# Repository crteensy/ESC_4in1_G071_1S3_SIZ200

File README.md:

# ESC_4in1_G071_1S3_SIZ200

## UNTESTED
The G071+NCP81161 combo was successfully tested (with PSMN1R8-30MLHX though).

## Description
KiCad project for a 20mm 4in1 ESC
- 4 layers for prototyping
- no part smaller than 0402
- 1-3 S
- STM32G071
- NCP81161 gate drivers
- SIZ200
- 0m5 current sense shunt with INA186
- 5V reg: TPS630701; max 2A (VBat = 5 V)

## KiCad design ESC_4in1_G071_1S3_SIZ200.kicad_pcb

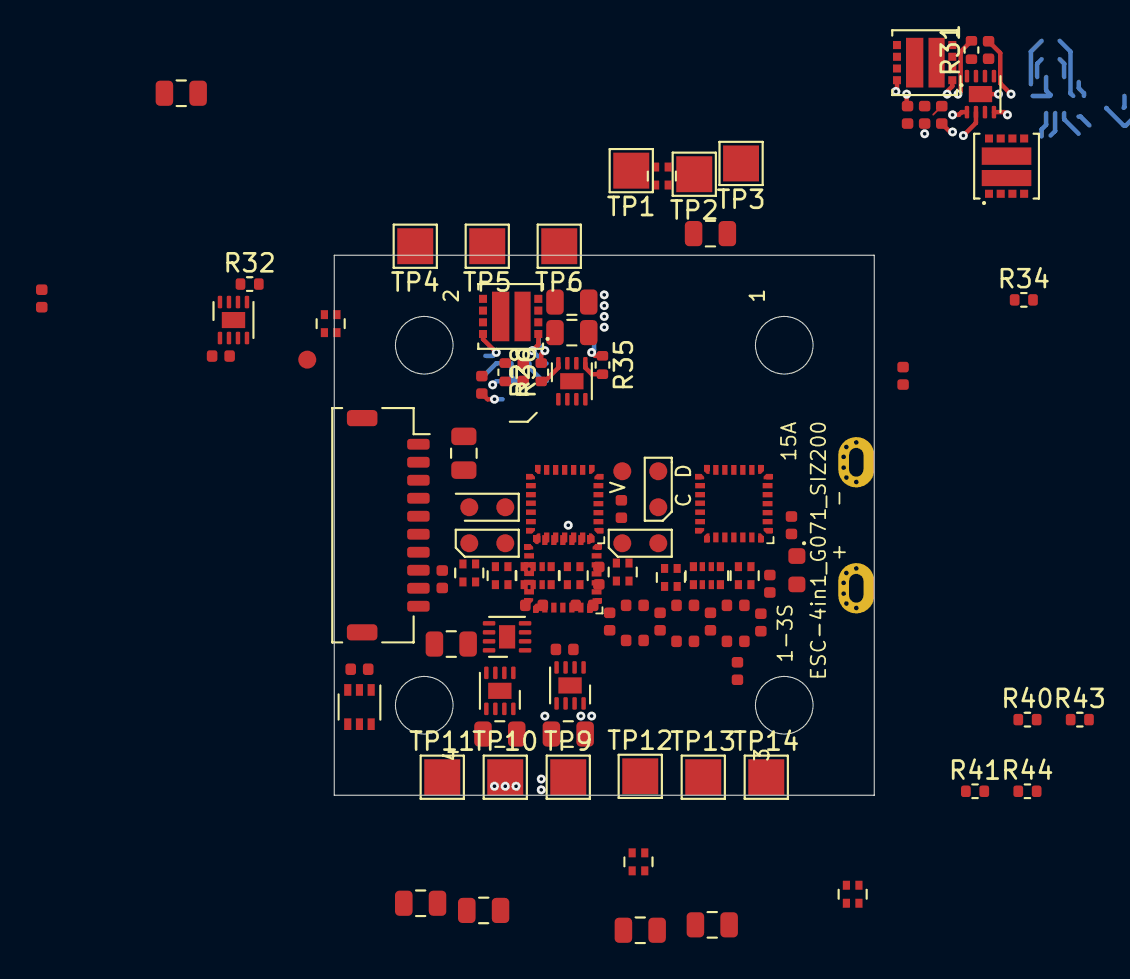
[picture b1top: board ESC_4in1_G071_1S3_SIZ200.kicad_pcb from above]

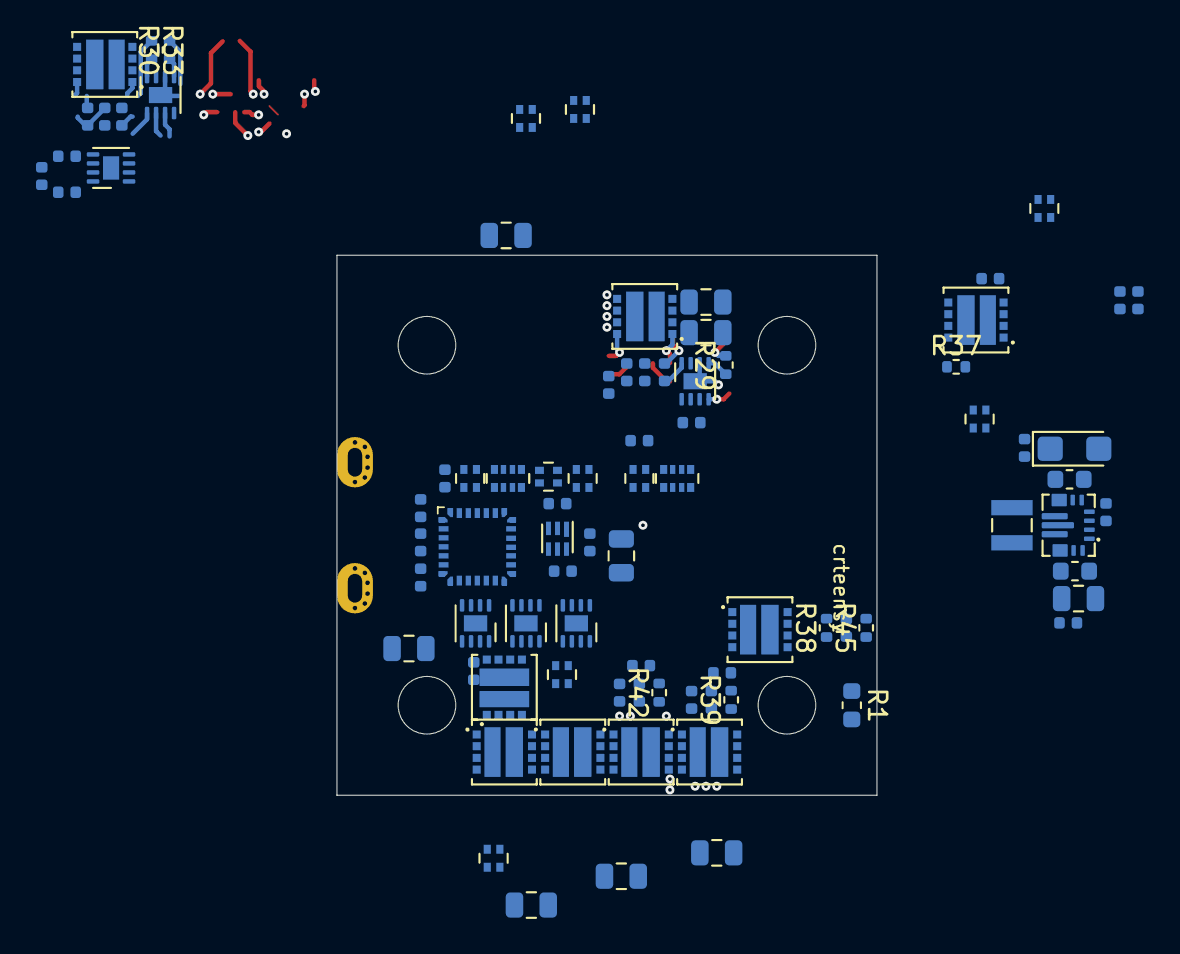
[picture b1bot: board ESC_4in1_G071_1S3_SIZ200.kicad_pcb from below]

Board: 6 copper layers, 30.0 x 30.0 mm, 191 parts (85 on the bottom side), 146 nets.

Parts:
C1, C2, C3, C8, C10, C12, C17, C21, C22, C24, C25, C27, C29, C31, C32, C34, C36, C63: 100n; C_0402_1005Metric
C4, C5, C6, C7, C9, C11, C23, C26, C28, C30, C33, C35: 1u; C_0402_1005Metric
C13: 10u; C_0805_2012Metric_dense
C14, C15: 10u; C_0603_1608Metric_dense
C16: 100u; CP_EIA-3216-10_Kemet-I
C18, C19: 2u2; C_0402_1005Metric
C20: 10n; C_0402_1005Metric
C37, C38, C39, C40, C41, C42, C43, C44, C45, C46, C47, C48, C49, C50, C51, C52, C53, C54, C55, C56: 22u; C_0805_2012Metric_dense
C70: 10u; C_0402_1005Metric
D1: LED; LED_0603_1608Metric
FB1, FB2: Ferrite_Bead_Small; L_0402_1005Metric
H1, H2, H3, H4: MountingHole; MountingHole_3.2mm_4mm
J1: Conn_01x10; JST_SHL_SM10B-SHLS-TF_1x10-1MP_P1.00mm_Horizontal_dense
L1: 820 nH; L_Wuerth_MAPI-2510
R1: 0m5; C_0603_1608Metric_dense
R2, R6, R10, R14, R18, R36, R37: 10k; R_0402_1005Metric
R3, R4, R5, R7, R8, R9, R11, R12, R13, R15, R16, R17: 4k7; R_0402_1005Metric
R19, R20, R21, R22, R23, R24, R25, R26, R28, R29, R30, R31, R32, R33, R34, R35, R38, R39, R40, R41, R42, R43, R44, R45: 10R0; R_0402_1005Metric
R27: 1k; R_0402_1005Metric
RN1, RN3, RN4, RN6, RN14, RN19, RN20, RN22: 10R0; R_Array_Convex_2x0402_dense
RN2, RN5, RN13, RN16: 1k; R_Array_Convex_2x0402_dense
RN7, RN11, RN17, RN23: 2k2; R_Array_Convex_2x0402_dense
RN8, RN10, RN15, RN21: 10k; R_Array_Convex_2x0402_dense
RN9, RN12, RN18, RN24: 2k2; R_Array_Convex_4x0402_dense
TP1, TP2, TP3, TP4, TP5, TP6, TP9, TP10, TP11, TP12, TP13, TP14: TestPoint_Flag; ESC_Pad_2.0x2.0mm
TP7, TP8: TestPoint_Flag; batt_pad_wide_relaxed
TP15, TP16, TP17, TP18, TP19, TP20, TP21, TP22, TP23, TP24: TestPoint; TestPoint_Pad_D1.0mm_dense
U1, U17, U21, U28: STM32G071GBU6; UFQFPN28
U2, U4, U6, U8, U10, U12, U18, U20, U23, U25, U27, U30: NCP81161MNTBG; DFN-8-1EP_2x2mm_P0.5mm_EP0.9x1.3mm_narrow
U3, U5, U7, U9, U11, U13, U19, U22, U24, U26, U29, U31: SIZ200DT-T1-GE3; PowerPAIR3.3x3.3_splitpaste
U14: TPS630701; TEXAS_15-VQFN-HR
U15: TPS72733DSE; WSON-6_1.5x1.5mm_P0.5mm
U16: INA186A2; SOT-363_SC-70-6

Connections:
+3V3: C19.2, C21.2, C22.2, C25.2, C32.2, C63.2, C70.2, D1.2, TP23.1, U1.3, U15.1, U17.3, U21.3, U28.3
+5V: C4.2, C5.2, C6.2, C7.2, C9.2, C11.2, C18.2, C23.2, C26.2, C28.2, C30.2, C33.2, C35.2, FB2.1, J1.9, R3.1, R4.1, R5.1, R7.1, R8.1, R9.1, R11.1, R12.1, R13.1, R15.1, R16.1, R17.1, U2.4, U4.4, U6.4, U8.4, U10.4, U12.4, U15.4, U15.6, U16.3, U18.4, U20.4, U23.4, U25.4, U27.4, U30.4
+BATT: C40.2, C41.2, C42.2, C43.2, C44.2, C45.2, C46.2, C47.2, C48.2, C49.2, C50.2, C51.2, C52.2, C53.2, C54.2, C55.2, C56.2, FB1.2, J1.2, R1.1, TP7.1, U3.2, U5.2, U7.2, U9.2, U11.2, U13.2, U16.4, U26.2, U29.2, U31.2
/ESC1_A: C1.1, RN8.2, TP1.1, U2.7, U3.3
/ESC1_A_DRVH: R33.2, U2.8
/ESC1_A_DRVL: R30.1, U2.5
/ESC1_A_EN: U1.22, U2.3
/ESC1_A_GH: R33.1, U3.1
/ESC1_A_GL: R30.2, U3.5
/ESC1_A_PWM: R3.2, U1.19, U2.2
/ESC1_B: C2.1, RN8.1, TP2.1, U4.7, U5.3
/ESC1_B_DRVH: R31.1, U4.8
/ESC1_B_DRVL: R26.2, U4.5
/ESC1_B_EN: U1.17, U4.3
/ESC1_B_GH: R31.2, U5.1
/ESC1_B_GL: R26.1, U5.5
/ESC1_B_PWM: R4.2, U1.18, U4.2
/ESC1_C: C3.1, R6.1, TP3.1, U6.7, U7.3
/ESC1_C_DRVH: R34.2, U6.8
/ESC1_C_DRVL: R22.2, U6.5
/ESC1_C_EN: U1.13, U6.3
/ESC1_C_GH: R34.1, U7.1
/ESC1_C_GL: R22.1, U7.5
/ESC1_C_PWM: R5.2, U1.16, U6.2
/ESC1_IN: RN13.4, U1.24
/ESC1_MA: RN8.3, RN9.1, RN9.2, U1.27
/ESC1_MB: RN8.4, RN9.3, RN9.4, U1.23
/ESC1_MC: R6.2, RN7.3, RN7.4, U1.8
/ESC1_SWDCLK: TP22.1, U1.21
/ESC1_SWDIO: TP20.1, U1.20
/ESC1_Y: RN7.1, RN9.6, RN9.8, U1.9
/ESC1_tele_o: RN2.4, U1.26
/ESC2_A: C8.1, R37.2, TP4.1, U8.7, U9.3
/ESC2_A_DRVH: R19.2, U8.8
/ESC2_A_DRVL: R32.2, U8.5
/ESC2_A_EN: U8.3, U17.22
/ESC2_A_GH: R19.1, U9.1
/ESC2_A_GL: R32.1, U9.5
/ESC2_A_PWM: R7.2, U8.2, U17.19
/ESC2_B: C10.1, R36.1, TP5.1, U10.7, U11.3
/ESC2_B_DRVH: R23.2, U10.8
/ESC2_B_DRVL: R29.1, U10.5
/ESC2_B_EN: U10.3, U17.17
/ESC2_B_GH: R23.1, U11.1
/ESC2_B_GL: R29.2, U11.5
/ESC2_B_PWM: R8.2, U10.2, U17.18
/ESC2_C: C12.1, R10.1, TP6.1, U12.7, U13.3
/ESC2_C_DRVH: R28.1, U12.8
/ESC2_C_DRVL: R35.2, U12.5
/ESC2_C_EN: U12.3, U17.13
/ESC2_C_GH: R28.2, U13.1
/ESC2_C_GL: R35.1, U13.5
/ESC2_C_PWM: R9.2, U12.2, U17.16
/ESC2_IN: RN13.3, U17.24
/ESC2_MA: R37.1, RN12.1, RN12.2, U17.27
/ESC2_MB: R36.2, RN12.3, RN12.4, U17.23
/ESC2_MC: R10.2, RN11.3, RN11.4, U17.8
/ESC2_SWDCLK: TP18.1, U17.21
/ESC2_SWDIO: TP16.1, U17.20
/ESC2_Y: RN11.1, RN12.6, RN12.8, U17.9
/ESC2_tele_o: RN2.3, U17.26
/ESC3_A: C31.1, RN21.1, TP12.1, U25.7, U26.3
/ESC3_A_DRVH: R43.2, U25.8
/ESC3_A_DRVL: R44.2, U25.5
/ESC3_A_EN: U25.3, U28.22
/ESC3_A_GH: R43.1, U26.1
/ESC3_A_GL: R44.1, U26.5
/ESC3_A_PWM: R15.2, U25.2, U28.19
/ESC3_B: C34.1, RN21.2, TP13.1, U27.7, U29.3
/ESC3_B_DRVH: R41.2, U27.8
/ESC3_B_DRVL: R25.2, U27.5
/ESC3_B_EN: U27.3, U28.17
/ESC3_B_GH: R41.1, U29.1
/ESC3_B_GL: R25.1, U29.5
/ESC3_B_PWM: R16.2, U27.2, U28.18
/ESC3_C: C36.1, R18.1, TP14.1, U30.7, U31.3
/ESC3_C_DRVH: R40.2, U30.8
/ESC3_C_DRVL: R21.2, U30.5
/ESC3_C_EN: U28.13, U30.3
/ESC3_C_GH: R40.1, U31.1
/ESC3_C_GL: R21.1, U31.5
/ESC3_C_PWM: R17.2, U28.16, U30.2
/ESC3_IN: RN16.4, U28.24
/ESC3_MA: RN21.4, RN24.1, RN24.2, U28.27
/ESC3_MB: RN21.3, RN24.3, RN24.4, U28.23
/ESC3_MC: R18.2, RN23.3, RN23.4, U28.8
/ESC3_SWDCLK: TP21.1, U28.21
/ESC3_SWDIO: TP19.1, U28.20
/ESC3_Y: RN23.1, RN24.6, RN24.8, U28.9
/ESC3_tele_o: RN5.4, U28.26
/ESC4_A: C24.1, RN15.1, TP9.1, U18.7, U19.3
/ESC4_A_DRVH: R24.2, U18.8
/ESC4_A_DRVL: R42.2, U18.5
/ESC4_A_EN: U18.3, U21.22
/ESC4_A_GH: R24.1, U19.1
/ESC4_A_GL: R42.1, U19.5
/ESC4_A_PWM: R11.2, U18.2, U21.19
/ESC4_B: C27.1, RN15.2, TP10.1, U20.7, U22.3
/ESC4_B_DRVH: R20.2, U20.8
/ESC4_B_DRVL: R39.2, U20.5
/ESC4_B_EN: U20.3, U21.17
/ESC4_B_GH: R20.1, U22.1
/ESC4_B_GL: R39.1, U22.5
/ESC4_B_PWM: R12.2, U20.2, U21.18
/ESC4_C: C29.1, R14.1, TP11.1, U23.7, U24.3
/ESC4_C_DRVH: R38.2, U23.8
/ESC4_C_DRVL: R45.2, U23.5
/ESC4_C_EN: U21.13, U23.3
/ESC4_C_GH: R38.1, U24.1
/ESC4_C_GL: R45.1, U24.5
/ESC4_C_PWM: R13.2, U21.16, U23.2
/ESC4_IN: RN16.3, U21.24
/ESC4_MA: RN15.4, RN18.1, RN18.2, U21.27
/ESC4_MB: RN15.3, RN18.3, RN18.4, U21.23
/ESC4_MC: R14.2, RN17.3, RN17.4, U21.8
/ESC4_SWDCLK: TP17.1, U21.21
/ESC4_SWDIO: TP15.1, U21.20
/ESC4_Y: RN17.1, RN18.6, RN18.8, U21.9
/ESC4_tele_o: RN5.3, U21.26
/ESCx_tele: J1.4, RN2.1, RN2.2, RN5.1, RN5.2
/IBat: C20.2, J1.3, R2.1
GND: C4.1, C5.1, C6.1, C7.1, C9.1, C11.1, C13.1, C14.1, C15.1, C16.2, C17.1, C18.1, C19.1, C20.1, C21.1, C22.1, C23.1, C25.1, C26.1, C28.1, C30.1, C32.1, C33.1, C35.1, C37.1, C38.1, C39.1, C40.1, C41.1, C42.1, C43.1, C44.1, C45.1, C46.1, C47.1, C48.1, C49.1, C50.1, C51.1, C52.1, C53.1, C54.1, C55.1, C56.1, C63.1, C70.1, J1.1, J1.10, R27.1, RN7.2, RN9.5, RN9.7, RN11.2, RN12.5, RN12.7, RN17.2, RN18.5, RN18.7, RN23.2, RN24.5, RN24.7, TP8.1, TP24.1, U1.4, U2.6, U2.9, U3.4, U4.6, U4.9, U5.4, U6.6, U6.9, U7.4, U8.6, U8.9, U9.4, U10.6, U10.9, U11.4, U12.6, U12.9, U13.4, U14.4, U14.6, U14.10, U14.15, U15.2, U15.3, U15.5, U16.1, U16.2, U17.4, U18.6, U18.9, U19.4, U20.6, U20.9, U21.4, U22.4, U23.6, U23.9, U24.4, U25.6, U25.9, U26.4, U27.6, U27.9, U28.4, U29.4, U30.6, U30.9, U31.4
unnamed: C1.2, U2.1
unnamed: C2.2, U4.1
unnamed: C3.2, U6.1
unnamed: C8.2, U8.1
unnamed: C10.2, U10.1
unnamed: C12.2, U12.1
unnamed: C13.2, C14.2, FB1.1, U14.1, U14.13, U14.14
unnamed: C15.2, C16.1, FB2.2, U14.5, U14.7
unnamed: C17.2, U14.3
unnamed: C24.2, U18.1
unnamed: C27.2, U20.1
unnamed: C29.2, U23.1
unnamed: C31.2, U25.1
unnamed: C34.2, U27.1
unnamed: C36.2, U30.1
unnamed: D1.1, R27.2
unnamed: J1.5, RN13.1
unnamed: J1.6, RN13.2
unnamed: J1.7, RN16.1
unnamed: J1.8, RN16.2
unnamed: L1.1, U14.9
unnamed: L1.2, U14.11
unnamed: R2.2, U16.6
VESC4: C37.2, C38.2, C39.2, R1.2, U16.5, U19.2, U22.2, U24.2

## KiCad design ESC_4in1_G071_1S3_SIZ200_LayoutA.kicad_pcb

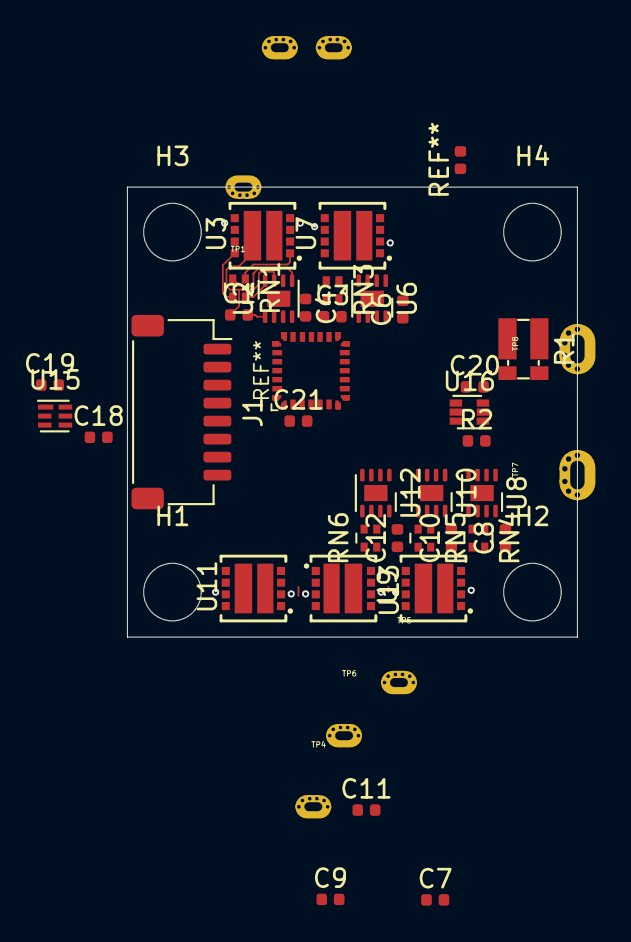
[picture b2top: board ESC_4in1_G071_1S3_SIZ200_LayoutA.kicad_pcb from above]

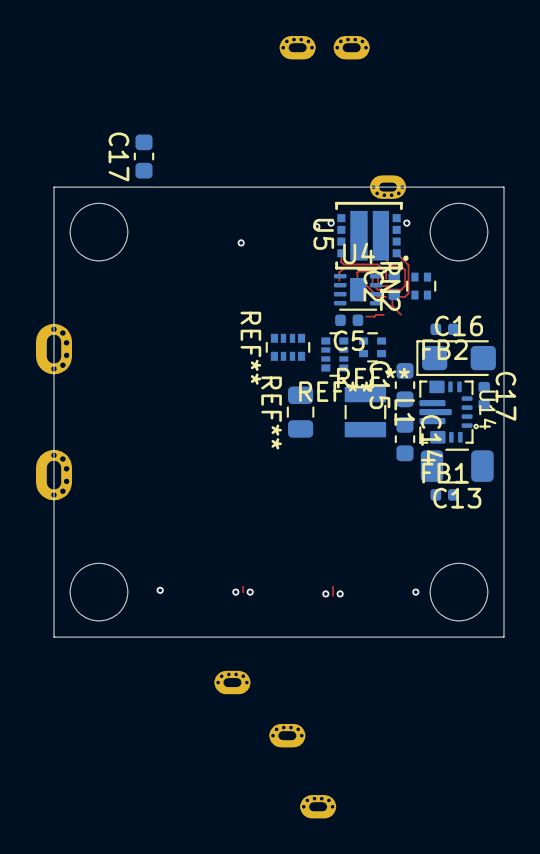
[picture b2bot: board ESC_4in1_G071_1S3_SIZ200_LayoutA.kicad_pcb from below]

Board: 2 copper layers, 25.0 x 25.0 mm, 62 parts (15 on the bottom side), 56 nets.

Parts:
C1, C2, C3, C4, C5, C6, C7, C8, C9, C10, C11, C12, C17, C21: 100n; C_0402_1005Metric
C13: 10u; C_1206_3216Metric_dense
C14, C15, C17#2: 10u; C_0603_1608Metric_dense
C16: 100u; CP_EIA-3216-10_Kemet-I
C18, C19: 2u2; C_0402_1005Metric
C20: 10n; C_0402_1005Metric
FB1, FB2: Ferrite_Bead_Small; L_0402_1005Metric
H1, H2, H3, H4: MountingHole; MountingHole_3.2mm_4mm
J1: Conn_01x08; JST_SH_SM08B-SRSS-TB_1x08-1MP_P1.00mm_Horizontal
L1: 1u; L_Wuerth_MAPI-2510
R1: R_Shunt; R_Shunt_Vishay_WSKW0612
R2: 10k; C_0402_1005Metric
RN1, RN2, RN3, RN4, RN5, RN6: 10R0; R_Array_Convex_2x0402
TP1, TP2, TP3, TP4, TP5, TP6: TestPoint_Flag; esc_pad
TP7, TP8: TestPoint_Flag; batt_pad_wide
U1: STM32G071GBU6; UFQFPN28
U2, U4, U6, U8, U10, U12: NCP81253MNTBG; DFN-8-1EP_2x2mm_P0.5mm_EP0.9x1.3mm_narrow
U3, U5, U7, U9, U11, U13: SIZ200DT-T1-GE3; PowerPAIR3.3x3.3
U14: TPS630701; TEXAS_15-VQFN-HR
U15: TPS727xxDSE; WSON-6_1.5x1.5mm_P0.5mm
U16: INA185; SOT-563

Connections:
+3V3: C19.2, C21.2, U15.1, U16.3
+5V: C4.2, C5.2, C6.2, C7.2, C9.2, C11.2, C18.2, FB2.1, U2.4, U4.4, U6.4, U8.4, U10.4, U12.4, U15.4, U15.6
+BATT: FB1.2, TP7.1, U3.2, U5.2, U7.2, U9.2, U11.2, U13.2
/ESC1_A: C1.1, TP1.1, U2.7, U3.3
/ESC1_A_EN: U1.15, U2.3
/ESC1_A_PWM: U1.19, U2.2
/ESC1_B: C2.1, TP2.1, U4.7, U5.3
/ESC1_B_EN: U1.14, U4.3
/ESC1_B_PWM: U1.18, U4.2
/ESC1_C: C3.1, TP3.1, U6.7, U7.3
/ESC1_C_EN: U1.13, U6.3
/ESC1_C_PWM: U1.16, U6.2
/ESC2_A: C8.1, TP4.1, U8.7, U9.3
/ESC2_B: C10.1, TP5.1, U10.7, U11.3
/ESC2_C: C12.1, TP6.1, U12.7, U13.3
/IBat: C20.2, R2.1
GND: C4.1, C5.1, C6.1, C7.1, C9.1, C11.1, C13.1, C14.1, C15.1, C16.2, C17.1, C18.1, C19.1, C20.1, C21.1, R1.4, U2.6, U2.9, U3.4, U4.6, U4.9, U5.4, U6.6, U6.9, U7.4, U8.6, U8.9, U9.4, U10.6, U10.9, U11.4, U12.6, U12.9, U13.4, U14.4, U14.6, U14.10, U14.15, U15.2, U15.3, U15.5, U16.1, U16.2
unnamed: C1.2, U2.1
unnamed: C2.2, U4.1
unnamed: C3.2, U6.1
unnamed: C8.2, U8.1
unnamed: C10.2, U10.1
unnamed: C12.2, U12.1
unnamed: C13.2, C14.2, FB1.1, U14.1, U14.13, U14.14
unnamed: C15.2, C16.1, FB2.2, U14.5, U14.7
unnamed: C17.2, U14.3
unnamed: L1.1, U14.9
unnamed: L1.2, U14.11
unnamed: R1.1, TP8.1
unnamed: R1.2, U16.4
unnamed: R1.3, U16.5
unnamed: R2.2, U16.6
unnamed: RN1.1, U3.1
unnamed: RN1.2, U2.5
unnamed: RN1.3, U3.5
unnamed: RN1.4, U2.8
unnamed: RN2.1, U4.8
unnamed: RN2.2, U4.5
unnamed: RN2.3, U5.5
unnamed: RN2.4, U5.1
unnamed: RN3.1, U7.1
unnamed: RN3.2, U6.5
unnamed: RN3.3, U7.5
unnamed: RN3.4, U6.8
unnamed: RN4.1, U9.1
unnamed: RN4.2, U8.5
unnamed: RN4.3, U9.5
unnamed: RN4.4, U8.8
unnamed: RN5.1, U10.8
unnamed: RN5.2, U10.5
unnamed: RN5.3, U11.5
unnamed: RN5.4, U11.1
unnamed: RN6.1, U13.5
unnamed: RN6.2, U13.1
unnamed: RN6.3, U12.8
unnamed: RN6.4, U12.5

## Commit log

2021-01-26 update schematic and layout
2021-01-31 update schematic
2021-02-01 - ESC1 pinout updated - ESC1 schematic done - ESC1 routed - increased PCB size to 26*27 mm
2021-02-01 - update schematic pdf
2021-02-10 update schematic pdf
2021-02-16 update design files
2021-02-20 update layout
2021-02-20 update schematic, layout and schematic pdf
2021-02-20 add 3d view png
2021-02-20 update readme, add 3d view
2021-02-20 remove backup layouts
2021-02-25 cosmetic update
2021-02-27 update schematic, layout and doc
2021-02-28 minor cosmetic updates
2021-02-28 remove extra files
2021-03-03 layout cosmetics
2021-03-05 layout cosmetics, new 3D view files
2021-03-14 update DCDC layout
2021-03-15 adjust motor pad connection polygons
2021-03-27 add aisler compatible layout
2021-04-19 general redesign 1 current sensor per ESC
2021-04-23 layout work
